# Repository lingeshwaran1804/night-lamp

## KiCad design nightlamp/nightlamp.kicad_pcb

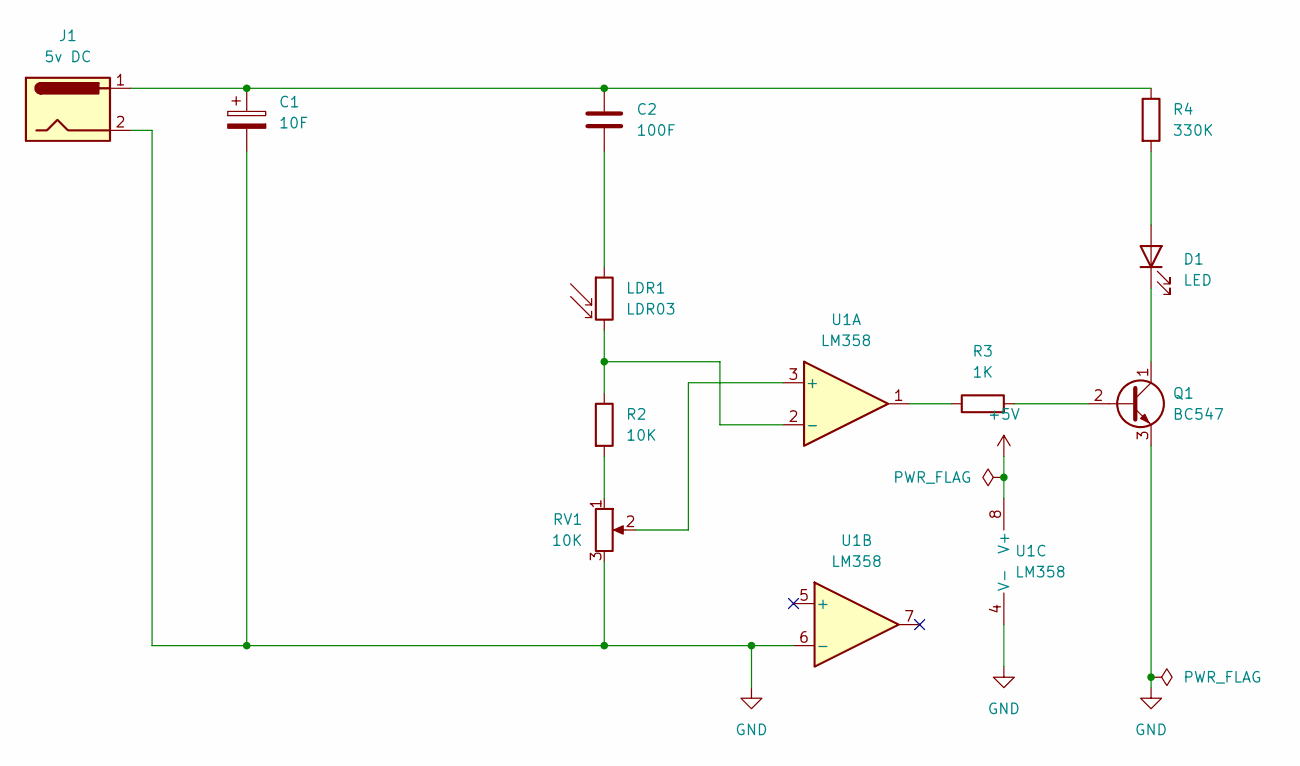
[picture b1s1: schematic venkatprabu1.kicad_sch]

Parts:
C1: 10F
C2: 100F
D1: LED
J1: 5v DC
LDR1: LDR03; R_LDR_10x8.5mm_P7.6mm_Vertical
Q1: BC547; TO-92_Inline
R2: 10K
R3: 1K
R4: 330K
RV1: 10K
U1: LM358

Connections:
+5V: U1.8 (V+)
GND: C1.2, J1.2, Q1.3 (E), RV1.3, U1.4 (V-), U1.6 (-)
unnamed: C1.1, C2.1, J1.1, R4.1
unnamed: C2.2, LDR1.1
unnamed: D1.2 (A), R4.2
unnamed: D1.1 (K), Q1.1 (C)
unnamed: Q1.2 (B), R3.2
unnamed: R2.2, RV1.1
unnamed: R3.1, U1.1
unnamed: RV1.2, U1.3 (+)
unnamed: LDR1.2, R2.1, U1.2 (-)

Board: 2 copper layers, 11 parts (0 on the bottom side), 10 nets, no tracks yet.
